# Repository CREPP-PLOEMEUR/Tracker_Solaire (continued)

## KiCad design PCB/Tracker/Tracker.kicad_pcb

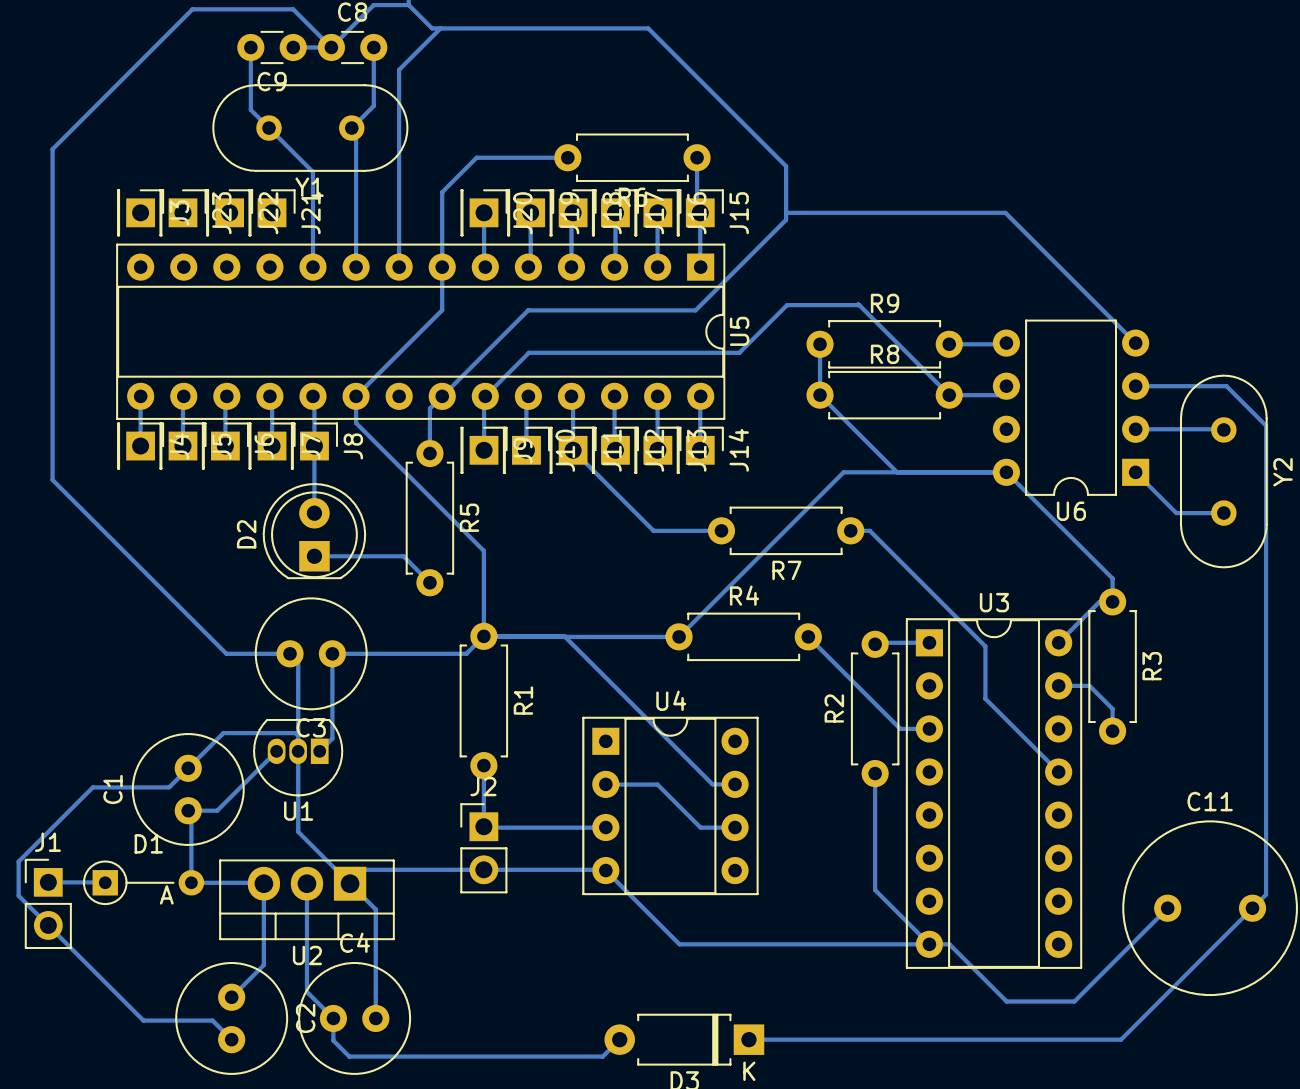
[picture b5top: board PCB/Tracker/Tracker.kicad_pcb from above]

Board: 2 copper layers, 50 parts (0 on the bottom side), 39 nets.

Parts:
C1, C2, C4: 100uF; C_Radial_D6.3mm_H11.0mm_P2.50mm
C3: 470uF; C_Radial_D6.3mm_H11.0mm_P2.50mm
C8, C9: 22pF; C_Disc_D3.0mm_W1.6mm_P2.50mm
C11: 1mF; C_Radial_D10.0mm_H16.0mm_P5.00mm
D1: DNF; D_DO-34_SOD68_P5.08mm_Vertical_AnodeUp
D2: LED; LED_D5.0mm
D3: D; D_A-405_P7.62mm_Horizontal
J1: Supply; PinHeader_1x02_P2.54mm_Vertical
J2: WindConnector; PinHeader_1x02_P2.54mm_Vertical
J3: D8; PinHeader_1x01_P2.54mm_Vertical
J4: D9; PinHeader_1x01_P2.54mm_Vertical
J5: D10; PinHeader_1x01_P2.54mm_Vertical
J6: D11; PinHeader_1x01_P2.54mm_Vertical
J7: D12; PinHeader_1x01_P2.54mm_Vertical
J8: D13; PinHeader_1x01_P2.54mm_Vertical
J9: A0; PinHeader_1x01_P2.54mm_Vertical
J10: A1; PinHeader_1x01_P2.54mm_Vertical
J11: A2; PinHeader_1x01_P2.54mm_Vertical
J12: A3; PinHeader_1x01_P2.54mm_Vertical
J13: A4; PinHeader_1x01_P2.54mm_Vertical
J14: A5; PinHeader_1x01_P2.54mm_Vertical
J15: RESET; PinHeader_1x01_P2.54mm_Vertical
J16: D0; PinHeader_1x01_P2.54mm_Vertical
J17: D1; PinHeader_1x01_P2.54mm_Vertical
J18: D2; PinHeader_1x01_P2.54mm_Vertical
J19: D3; PinHeader_1x01_P2.54mm_Vertical
J20: D4; PinHeader_1x01_P2.54mm_Vertical
J21: D5; PinHeader_1x01_P2.54mm_Vertical
J22: D6; PinHeader_1x01_P2.54mm_Vertical
J23: D7; PinHeader_1x01_P2.54mm_Vertical
R1: 100k; R_Axial_DIN0207_L6.3mm_D2.5mm_P7.62mm_Horizontal
R2, R3, R7: R; R_Axial_DIN0207_L6.3mm_D2.5mm_P7.62mm_Horizontal
R4, R6: 10k; R_Axial_DIN0207_L6.3mm_D2.5mm_P7.62mm_Horizontal
R5: 270; R_Axial_DIN0207_L6.3mm_D2.5mm_P7.62mm_Horizontal
R8, R9: 4.7k; R_Axial_DIN0207_L6.3mm_D2.5mm_P7.62mm_Horizontal
U1: L78L05_TO92; TO-92_Inline
U2: LT1083-3.3; TO-220-3_Vertical
U3: 74HCT123; DIP-16_W7.62mm_Socket
U4: TL081; DIP-8_W7.62mm_Socket
U5: ATmega328-PU; DIP-28_W7.62mm_Socket
U6: DS1307+; DIP-8_W7.62mm
Y1: Crystal; Crystal_HC49-4H_Vertical
Y2: Crystal; Crystal_HC18-U_Vertical

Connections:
+3V3: C4.1, D3.2 (A), U2.2 (VO)
+5V: C3.1, R1.1, R3.1, R4.1, R6.2, R8.1, R9.1, U1.1 (VO), U3.16 (VCC), U4.7 (V+), U5.7 (VCC), U5.20 (AVCC), U6.8 (VCC)
+12V: D1.1 (K), J1.1
A0_SCL: J9.1, R8.2, U5.23 (PC0), U6.6 (SCL)
A0_SDA: R9.2, U6.5 (SDA)
A1_SDA: J10.1, U5.24 (PC1)
A2_WIND: J11.1, R7.2, U5.25 (PC2)
A3: J12.1, U5.26 (PC3)
A4: J13.1, U5.27 (PC4)
A5: J14.1, U5.28 (PC5)
D0: J16.1, U5.2 (PD0)
D1: J17.1, U5.3 (PD1)
D2: J18.1, U5.4 (PD2)
D3: J19.1, U5.5 (PD3)
D4: J20.1, U5.6 (PD4)
D5: J21.1, U5.11 (PD5)
D6: J22.1, U5.12 (PD6)
D7: J23.1, U5.13 (PD7)
D8: J3.1, U5.14 (PB0)
D9: J4.1, U5.15 (PB1)
D10: J5.1, U5.16 (PB2)
D11: J6.1, U5.17 (PB3)
D12: J7.1, U5.18 (PB4)
D13_LED: D2.2 (A), J8.1, U5.19 (PB5)
GND: C1.2, C2.2, C3.2, C4.2, C8.1, C9.1, C11.1, J1.2, J2.2, R2.1, R5.1, U1.2 (GND), U2.1 (GND), U3.8 (GND), U4.4 (V-), U5.8 (GND), U5.22 (GND), U6.4 (GND)
unnamed: C1.1, C2.1, D1.2 (A), U1.3 (VI), U2.3 (VI)
unnamed: U4.2 (-), U4.6
unnamed: R2.2, U3.1 (A)
unnamed: R3.2, U3.15 (RCext)
unnamed: R4.2, U3.3 (Clr)
unnamed: C11.2, D3.1 (K), U6.3 (VBAT)
unnamed: D2.1 (K), R5.2
unnamed: J2.1, R1.2, U4.3 (+)
unnamed: R7.1, U3.13 (Q)
unnamed: U6.1 (X1), Y2.2
unnamed: U6.2 (X2), Y2.1
RESET: J15.1, R6.1, U5.1 (~RESET/PC6)
X1: C8.2, U5.9 (XTAL1/PB6), Y1.1
X2: C9.2, U5.10 (XTAL2/PB7), Y1.2

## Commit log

2023-01-20 Add initial files
2023-01-21 Update of PDF file
2023-02-05 Add some files
2023-08-27 Add PCB
2023-08-29 Add first code
2023-09-22 Add PCB with GNSS
2023-11-29 Update of repository
2023-12-04 Update GNSS
2024-01-21 forgot changes
2024-01-21 Udpate firmware
2024-01-21 Update and checking some GNSS positions
2024-01-22 update of directory
2024-03-06 Update of PCB
2024-03-17 Update PCB of Motor controller - version sent on production (debug purpose)
2024-05-28 Add CMS version
2024-09-15 Update 4Layers
